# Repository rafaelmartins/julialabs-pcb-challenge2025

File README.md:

# julialabs-pcb-challenge2025

Meu projeto do Julialabs PCB Challenge 2025.

Placa de circuito impresso baseada no formato de um cartão de visitas tradicional, implementando um sintetizador digital polifônico completo, com mini teclado e alto falante embutidos e saída de audio em linha para gravações.

> [!NOTE]
> **Recursos Externos**
>
> - [Apresentação](https://rafaelmartins.com/s/julialabs-pcb-challenge-2025/)
> - [Lista de Componentes na Mouser](https://www.mouser.de/api/CrossDomain/GetContext?syncDomains=www&returnUrl=https%3a%2f%2fwww.mouser.com%2fTools%2fProject%2fShare%3fAccessID%3d8af25229f1&async=False&setPrefSub=False&clearPrefSub=False)

## Revisão `20250818`

- [Lista Interativa de Materiais](https://rafaelmartins.github.io/julialabs-pcb-challenge2025/business-card-synth.html)
- [Diagrama Esquemático](https://rafaelmartins.github.io/julialabs-pcb-challenge2025/business-card-synth.pdf)
- [Arquivos Gerber](https://github.com/rafaelmartins/julialabs-pcb-challenge2025/blob/main/pcb/gerber/business-card-synth_rev20250818.zip)

## Licença

O projeto de hardware esta disponível a partir de uma [Licença CERN-OHL-S-2.0](LICENSE).

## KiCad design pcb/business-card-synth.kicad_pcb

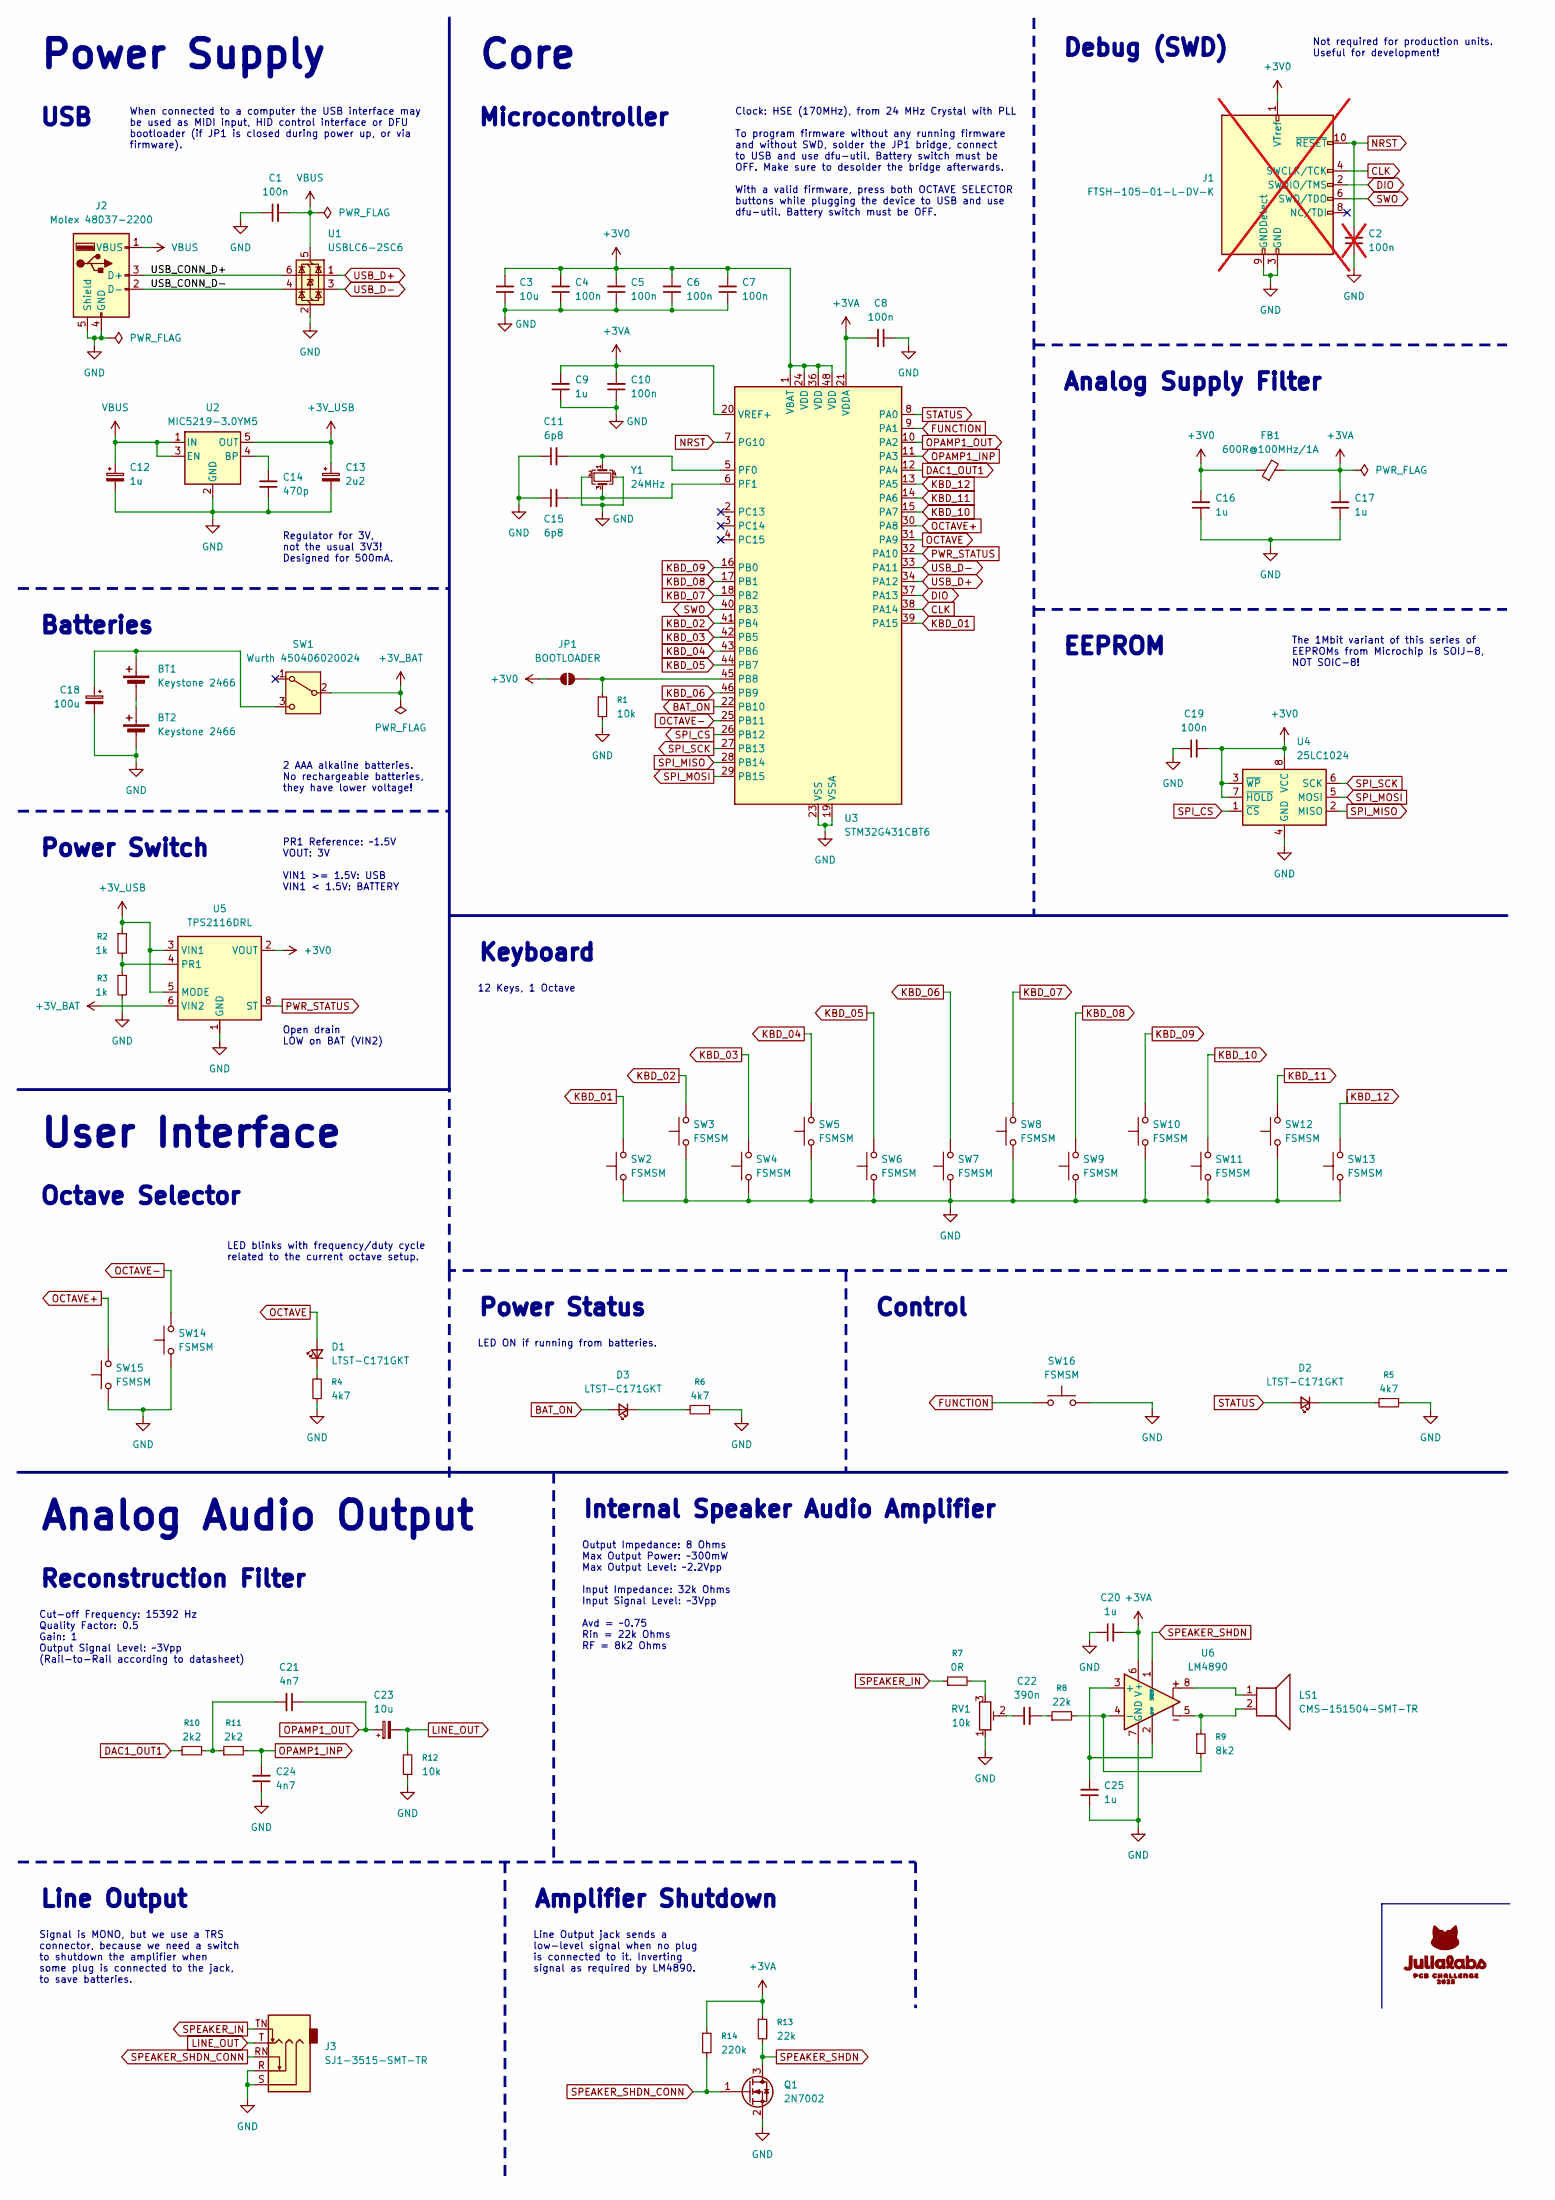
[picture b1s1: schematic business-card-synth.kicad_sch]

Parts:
BT1, BT2: Keystone 2466; BatteryHolder_Keystone_2466_1xAAA; Mouser No. 534-2466
C1, C4, C5, C6, C7, C8, C10, C19: 100n; C_0805_2012Metric; Mouser No. 603-CC805KRX7R9BB104
C2: 100n; C_0805_2012Metric; Mouser No. 603-CC805KRX7R9BB104; not fitted
C3: 10u; C_0805_2012Metric; Mouser No. 603-CC805KKX7R6BB106
C9, C16, C17, C20, C25: 1u; C_0805_2012Metric; Mouser No. 603-CC805KKX7R7BB105
C11, C15: 6p8; C_0603_1608Metric; Mouser No. 603-CC603CRNPO9BN6R8
C12: 1u; CP_EIA-3216-18_Kemet-A; Mouser No. 80-T491A105K25AT7280
C13: 2u2; CP_EIA-3216-18_Kemet-A; Mouser No. 80-T491A225K25AT7280
C14: 470p; C_0603_1608Metric; Mouser No. 603-C0603JRNPO9BN471
C18: 100u; CP_Elec_6.3x5.8; Mouser No. 710-875105344010
C21, C24: 4n7; C_1206_3216Metric; Mouser No. 667-ECH-U1H472JX5
C22: 390n; C_0805_2012Metric; Mouser No. 603-CC805KKX7R7BB394
C23: 10u; CP_Elec_6.3x5.8; Mouser No. 710-875105544001
D1, D2, D3: LTST-C171GKT; LED_0805_2012Metric_Pad1.15x1.40mm_HandSolder; Mouser No. 859-LTST-C171GKT
FB1: 600R@100MHz/1A; L_0805_2012Metric; Mouser No. 660-CZP2AFTTD601P
J1: FTSH-105-01-L-DV-K; Connector_Samtec_FTSH-105-01-L-DV-K; Mouser No. 200-FTSH10501LDVK; not fitted
J2: Molex 48037-2200; USB_A_Molex_48037-2200_Horizontal; Mouser No. 538-48037-2200
J3: SJ1-3515-SMT-TR; Jack_3.5mm_SameSky_SJ1-3515-SMT_Horizontal; Mouser No. 490-SJ1-3515-SMT-TR
JP1: BOOTLOADER; SolderJumper-2_P1.3mm_Open_TrianglePad1.0x1.5mm
LS1: CMS-151504-SMT-TR; Speaker_SameSky_CMS-151504-SMT-TR; Mouser No. 179-CMS-151504-SMTTR
Q1: 2N7002; SOT-23; Mouser No. 610-2N7002
R1, R12: 10k; R_0805_2012Metric; Mouser No. 603-AC0805FR-0710KL
R2, R3: 1k; R_0805_2012Metric; Mouser No. 603-AC0805FR-071KL
R4, R5, R6: 4k7; R_0805_2012Metric; Mouser No. 603-AC0805FR-074K7L
R7: 0R; R_0805_2012Metric; Mouser No. 603-AC0805FR-070RL
R8, R13: 22k; R_0805_2012Metric; Mouser No. 603-AC0805FR-0722KL
R9: 8k2; R_0805_2012Metric; Mouser No. 603-AC0805FR-078K2L
R10, R11: 2k2; R_0805_2012Metric; Mouser No. 603-AC0805FR-072K2L
R14: 220k; R_0805_2012Metric; Mouser No. 603-AC0805FR-07220KL
RV1: 10k; Potentiometer_Bourns_3306F_Horizontal; Mouser No. 652-3306F-1-103
SW1: Wurth 450406020024; SW_SPDT_Wurth_450406020024; Mouser No. 710-450406020024
SW2, SW3, SW4, SW5, SW6, SW7, SW8, SW9, SW10, SW11, SW12, SW13, SW14, SW15, SW16: FSMSM; SW_SPST_FSMSM; Mouser No. 506-FSMSM
U1: USBLC6-2SC6; SOT-23-6; Mouser No. 511-USBLC6-2SC6
U2: MIC5219-3.0YM5; SOT-23-5; Mouser No. 998-MIC5219-3.0YM5TR
U3: STM32G431CBT6; LQFP-48_7x7mm_P0.5mm; Mouser No. 511-STM32G431CBT6
U4: 25LC1024; SOIC-8_5.3x5.3mm_P1.27mm; Mouser No. 579-25LC1024-E/SM
U5: TPS2116DRL; SOT-583-8; Mouser No. 595-TPS2116DRLR
U6: LM4890; SOIC-8_3.9x4.9mm_P1.27mm; Mouser No. 926-LM4890MX/NOPB
Y1: 24MHz; Crystal_SMD_2016-4Pin_2.0x1.6mm; Mouser No. 344-CS10820-24M

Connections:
+3V0: C3.2, C4.2, C5.2, C6.2, C7.2, C16.2, C19.2, FB1.1, J1.1 (VTref), JP1.1 (A), U3.1 (VBAT), U3.24 (VDD), U3.36 (VDD), U3.48 (VDD), U4.3 (~WP), U4.7 (~HOLD), U4.8 (VCC), U5.2 (VOUT), U5.7 (VOUT)
+3VA: C8.2, C9.2, C10.2, C17.2, C20.2, FB1.2, R13.1, R14.1, U3.20 (VREF+), U3.21 (VDDA), U6.6 (V+)
+3V_BAT: SW1.2 (B), U5.6 (VIN2)
+3V_USB: C13.1, R2.1, U2.5 (OUT), U5.3 (VIN1), U5.5 (MODE)
/USB_CONN_D+: J2.3 (D+), U1.6 (I/O1)
/USB_CONN_D-: J2.2 (D-), U1.4 (I/O2)
BAT_ON: D3.2 (A), U3.22 (PB10)
CLK: J1.4 (SWCLK/TCK), U3.38 (PA14)
DAC1_OUT1: R10.1, U3.12 (PA4)
DIO: J1.2 (SWDIO/TMS), U3.37 (PA13)
FUNCTION: SW16.2, U3.9 (PA1)
GND: BT2.2 (-), C1.1, C2.1, C3.1, C4.1, C5.1, C6.1, C7.1, C8.1, C9.1, C10.1, C11.1, C12.2, C13.2, C14.1, C15.1, C16.1, C17.1, C18.2, C19.1, C20.1, C24.1, C25.1, J1.3 (GND), J1.5 (GND), J1.9 (GNDDetect), J2.4 (GND), J2.5 (Shield), J3.R, J3.S, Q1.2 (S), R1.2, R3.2, R4.1, R5.1, R6.1, R12.1, RV1.1, SW2.1, SW3.1, SW4.1, SW5.1, SW6.1, SW7.1, SW8.1, SW9.1, SW10.1, SW11.1, SW12.1, SW13.1, SW14.1, SW15.1, SW16.1, U1.2 (GND), U2.2 (GND), U3.19 (VSSA), U3.23 (VSS), U3.35 (VSS), U3.47 (VSS), U4.4 (GND), U5.1 (GND), U6.7 (GND), Y1.2, Y1.4
KBD_01: SW2.2, U3.39 (PA15)
KBD_02: SW3.2, U3.41 (PB4)
KBD_03: SW4.2, U3.42 (PB5)
KBD_04: SW5.2, U3.43 (PB6)
KBD_05: SW6.2, U3.44 (PB7)
KBD_06: SW7.2, U3.46 (PB9)
KBD_07: SW8.2, U3.18 (PB2)
KBD_08: SW9.2, U3.17 (PB1)
KBD_09: SW10.2, U3.16 (PB0)
KBD_10: SW11.2, U3.15 (PA7)
KBD_11: SW12.2, U3.14 (PA6)
KBD_12: SW13.2, U3.13 (PA5)
LINE_OUT: C23.2, J3.T, R12.2
NRST: C2.2, J1.10 (~RESET), U3.7 (PG10)
unnamed: BT1.1 (+), C18.1, SW1.3 (C)
unnamed: BT1.2 (-), BT2.1 (+)
unnamed: C21.2, R10.2, R11.1
unnamed: C22.1, RV1.2
unnamed: C22.2, R8.1
unnamed: D1.1 (K), R4.2
unnamed: D2.1 (K), R5.2
unnamed: D3.1 (K), R6.2
unnamed: JP1.2 (B), R1.1, U3.45 (PB8)
unnamed: LS1.1, U6.8
unnamed: LS1.2, R9.1, U6.5
unnamed: R7.2, RV1.3
unnamed: C14.2, U2.4 (BP)
unnamed: C11.2, U3.5 (PF0), Y1.1
unnamed: C15.2, U3.6 (PF1), Y1.3
unnamed: R2.2, R3.1, U5.4 (PR1)
unnamed: C25.2, U6.2 (BYP), U6.3 (+)
unnamed: R8.2, R9.2, U6.4 (-)
OCTAVE: D1.2 (A), U3.31 (PA9)
OCTAVE+: SW15.2, U3.30 (PA8)
OCTAVE-: SW14.2, U3.25 (PB11)
OPAMP1_INP: C24.2, R11.2, U3.11 (PA3)
OPAMP1_OUT: C21.1, C23.1, U3.10 (PA2)
PWR_STATUS: U3.32 (PA10), U5.8 (ST)
SPEAKER_IN: J3.TN, R7.1
SPEAKER_SHDN: Q1.3 (D), R13.2, U6.1 (~SHDN)
SPEAKER_SHDN_CONN: J3.RN, Q1.1 (G), R14.2
SPI_CS: U3.26 (PB12), U4.1 (~CS)
SPI_MISO: U3.28 (PB14), U4.2 (MISO)
SPI_MOSI: U3.29 (PB15), U4.5 (MOSI)
SPI_SCK: U3.27 (PB13), U4.6 (SCK)
STATUS: D2.2 (A), U3.8 (PA0)
SWO: J1.6 (SWO/TDO), U3.40 (PB3)
USB_D+: U1.1 (I/O1), U3.34 (PA12)
USB_D-: U1.3 (I/O2), U3.33 (PA11)
VBUS: C1.2, C12.1, J2.1 (VBUS), U1.5 (VBUS), U2.1 (IN), U2.3 (EN)

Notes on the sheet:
Clock: HSE (170MHz), from 24 MHz Crystal with PLL To program firmware without any running firmware and without SWD, solder the JP1 bridge, connect to USB and use dfu-util. Battery switch must be OFF. Make sure to desolder the bridge afterwards. With a valid firmware, press both OCTAVE SELECTOR butt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
Power Status
Internal Speaker Audio Amplifier
Line Output
2 AAA alkaline batteries. No rechargeable batteries, they have lower voltage!
Line Output jack sends a low-level signal when no plug is connected to it. Inverting signal as required by LM4890.
Open drain LOW on BAT (VIN2)
Control
Regulator for 3V, not the usual 3V3! Designed for 500mA.
Analog Audio Output
USB
Signal is MONO, but we use a TRS connector, because we need a switch to shutdown the amplifier when some plug is connected to the jack, to save batteries.
12 Keys, 1 Octave
PR1 Reference: ~1.5V VOUT: 3V VIN1 >= 1.5V: USB VIN1 < 1.5V: BATTERY
Microcontroller
Analog Supply Filter
When connected to a computer the USB interface may be used as MIDI input, HID control interface or DFU bootloader (if JP1 is closed during power up, or via firmware).
LED ON if running from batteries.
Keyboard
The 1Mbit variant of this series of EEPROMs from Microchip is SOIJ-8, NOT SOIC-8!
Debug (SWD)
Power Supply
EEPROM
Batteries
Octave Selector
Cut-off Frequency: 15392 Hz Quality Factor: 0.5 Gain: 1 Output Signal Level: ~3Vpp (Rail-to-Rail according to datasheet)
User Interface
Power Switch
Output Impedance: 8 Ohms Max Output Power: ~300mW Max Output Level: ~2.2Vpp Input Impedance: 32k Ohms Input Signal Level: ~3Vpp Avd = ~0.75 Rin = 22k Ohms RF = 8k2 Ohms
Not required for production units. Useful for development!
Core
Amplifier Shutdown
Reconstruction Filter
LED blinks with frequency/duty cycle related to the current octave setup.

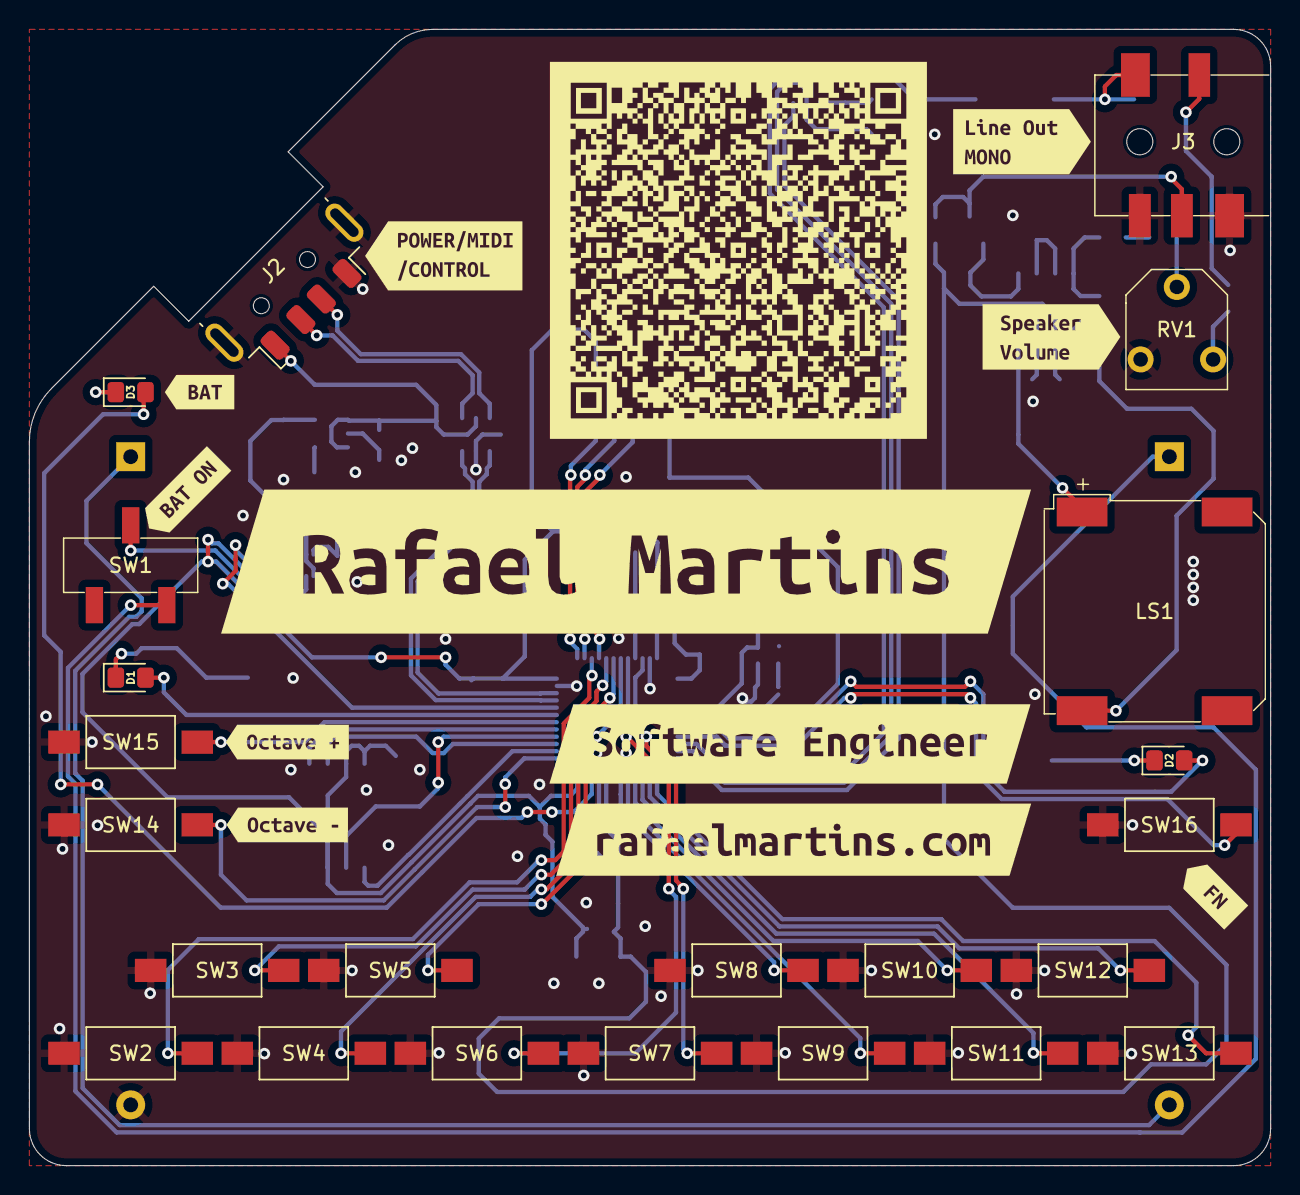
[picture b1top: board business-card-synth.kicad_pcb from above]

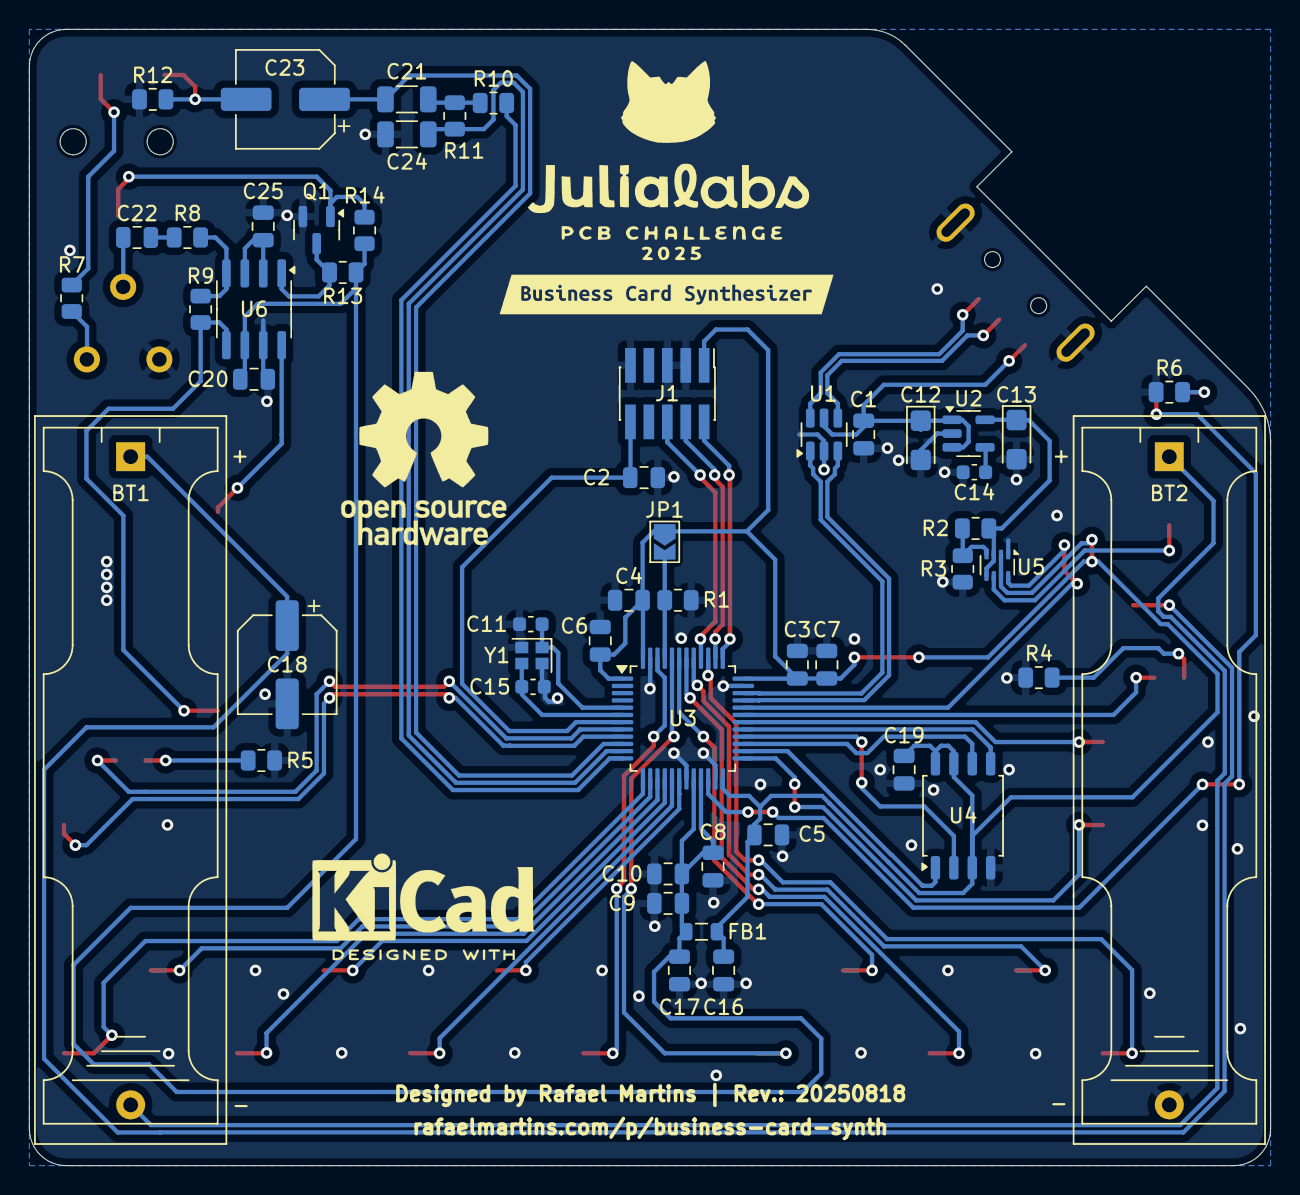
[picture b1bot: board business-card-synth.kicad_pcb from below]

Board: 2 copper layers, 85.6 x 78.4 mm, 87 parts (53 on the bottom side), 62 nets.

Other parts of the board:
kibuzzard-68A13B7B: G***; kibuzzard-68A13B7B
kibuzzard-68A26CA8: G***; kibuzzard-68A26CA8
kibuzzard-68A26E1C: G***; kibuzzard-68A26E1C
kibuzzard-68A29CF7: G***; kibuzzard-68A29CF7
kibuzzard-68A2383A: G***; kibuzzard-68A2383A
kibuzzard-68A23822: G***; kibuzzard-68A23822
kibuzzard-687D9D5C: G***; kibuzzard-687D9D5C
kibuzzard-687D97D9: G***; kibuzzard-687D97D9
kibuzzard-687D98B0: G***; kibuzzard-687D98B0
kibuzzard-687DA195: G***; kibuzzard-687DA195
kibuzzard-687EEB56: G***; kibuzzard-687EEB56
kibuzzard-687FF431: G***; kibuzzard-687FF431

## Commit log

2025-08-19 Commit inicial
2025-08-19 pequenas correcoes
2025-08-19 tentando renderizar a pcb com solder mask preta
2025-08-19 usar preset novo no kicad-cli
2025-08-19 typo
2025-08-19 corrigir cores do preset

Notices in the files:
pcb/business-card-synth.kicad_pcb:
Released under CERN Open Hardware Licence Version 2 - Strongly Reciprocal
